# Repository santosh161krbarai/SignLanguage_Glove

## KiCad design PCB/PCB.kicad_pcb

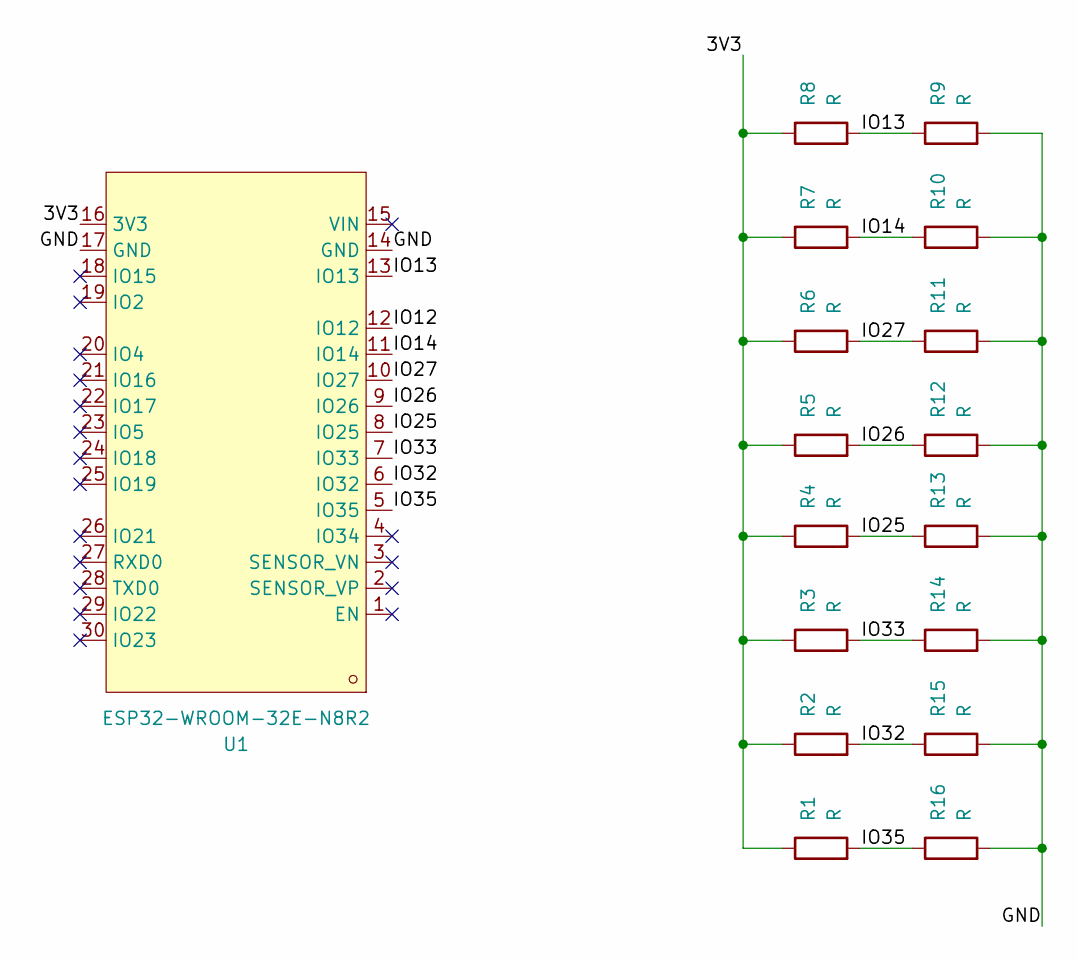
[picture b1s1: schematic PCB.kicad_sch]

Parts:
R1, R2, R3, R4, R5, R6, R7, R8, R9, R10, R11, R12, R13, R14, R15, R16: R; R_Axial_DIN0207_L6.3mm_D2.5mm_P10.16mm_Horizontal
U1: ESP32-WROOM-32E-N8R2; esp32 dev board; LCSC Part C5361945

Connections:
/3V3: R1.1, R2.1, R3.1, R4.1, R5.1, R6.1, R7.1, R8.1, U1.16 (3V3)
/GND: R9.2, R10.2, R11.2, R12.2, R13.2, R14.2, R15.2, R16.2, U1.14 (GND), U1.17 (GND)
/IO12: U1.12 (IO12)
/IO13: R8.2, R9.1, U1.13 (IO13)
/IO14: R7.2, R10.1, U1.11 (IO14)
/IO25: R4.2, R13.1, U1.8 (IO25)
/IO26: R5.2, R12.1, U1.9 (IO26)
/IO27: R6.2, R11.1, U1.10 (IO27)
/IO32: R2.2, R15.1, U1.6 (IO32)
/IO33: R3.2, R14.1, U1.7 (IO33)
/IO35: R1.2, R16.1, U1.5 (IO35)

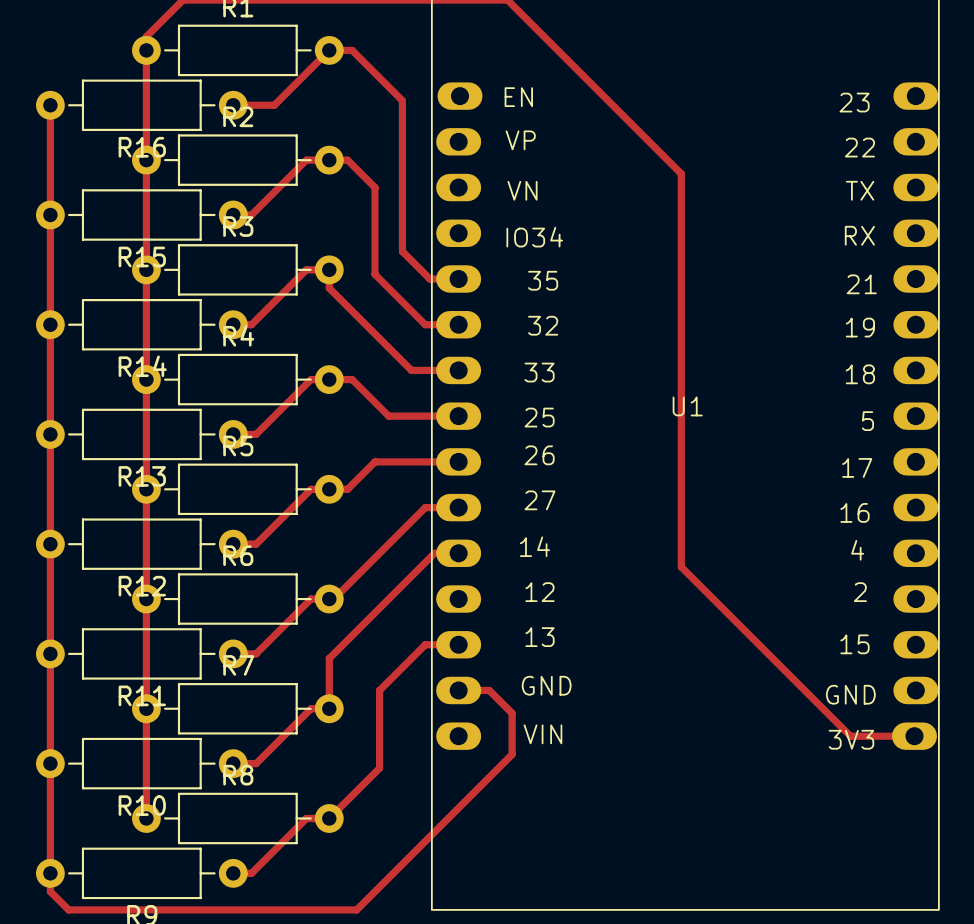
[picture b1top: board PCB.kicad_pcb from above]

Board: 2 copper layers, 17 parts (0 on the bottom side), 10 nets.

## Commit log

2025-09-30 first push
2025-12-07 Add project description to README
